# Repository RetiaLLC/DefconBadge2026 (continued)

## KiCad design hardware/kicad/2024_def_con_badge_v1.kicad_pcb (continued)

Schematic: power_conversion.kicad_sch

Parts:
C13, C14, C15, C18, C19: 10uF; C_0603_1608Metric_Pad1.08x0.95mm_HandSolder; LCSC Part # C326057
C16: 4.7uF; C_0603_1608Metric_Pad1.08x0.95mm_HandSolder; LCSC Part # C326580
C17: 0.1uF; C_0603_1608Metric_Pad1.08x0.95mm_HandSolder; LCSC Part # C92490
D10: D; D_SMA; LCSC Part # C50645
L1: 1uH; koher_MDA4020_series_inductor; LCSC Part # C2847468
L2: 2.2uH; koher_MDA4020_series_inductor; LCSC Part # C2847469
Q4: Q_NMOS_GSD; LCSC_SOT-23; LCSC Part # C91714
R27: 750K; R_0603_1608Metric_Pad0.98x0.95mm_HandSolder; LCSC Part # C137684
R28, R31: 100K; R_0603_1608Metric_Pad0.98x0.95mm_HandSolder; LCSC Part # C14675
R30: 453K; R_0603_1608Metric_Pad0.98x0.95mm_HandSolder; LCSC Part # C227908
R32: 330R; R_0603_1608Metric_Pad0.98x0.95mm_HandSolder; LCSC Part # C105881
R33, R34: 10K; R_0603_1608Metric_Pad0.98x0.95mm_HandSolder; LCSC Part # C98220
U4: TPS61023DRLR; TI_CONVERTER_SOT563; LCSC Part # C919459
U5: TLV62569DBV; LCSC_SOT-23-5; LCSC Part # C141836

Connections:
+3.3V: C18.1, C19.1, L2.2, R30.1; also elsewhere on the board
+5V: C14.1, C15.1, C16.1, C17.1, D10.1 (K), R27.1, U4.6 (VOUT), U5.1 (EN), U5.4 (VIN); also elsewhere on the board
/buttons/+BATT: C13.1, L1.1, R34.1, U4.3 (VIN); also elsewhere on the board
/buttons/+USB_IN: D10.2 (A), R32.1; also elsewhere on the board
/power_conversion/stepup_conv_en: Q4.3 (D), R34.2, U4.2 (EN)
GND: C13.2, C14.2, C15.2, C16.2, C17.2, C18.2, C19.2, Q4.2 (S), R28.2, R31.2, R33.1, U4.4 (GND), U5.2 (GND); also elsewhere on the board
unnamed: Q4.1 (G), R32.2, R33.2
unnamed: R27.2, R28.1, U4.1 (FB)
unnamed: L1.2, U4.5 (SW)
unnamed: R30.2, R31.1, U5.5 (FB)
unnamed: L2.1, U5.3 (SW)

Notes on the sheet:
step-down
step-up
diode
"R2"
+5v
0.6 * [1 + (453k/100k)] = 3.318V
Vref = 0.6V [(5/0.6) - 1]*100k = 733kohm
STEP-UP CONVERTER
STEP-DOWN CONVERTER
"R1"
R1/R2 need to be 0.1% resistors to ensure output accuracy
Set to 5.1V to ensure biasing of diode with usb power
-----General concept for power layout----- Diode prevents fighting between usb and dc/dc converter step-up converter only on when usb power is disconnected
AAs
STEP-UP CONVERTER ENABLE
USB POWER
usb
+3.3v

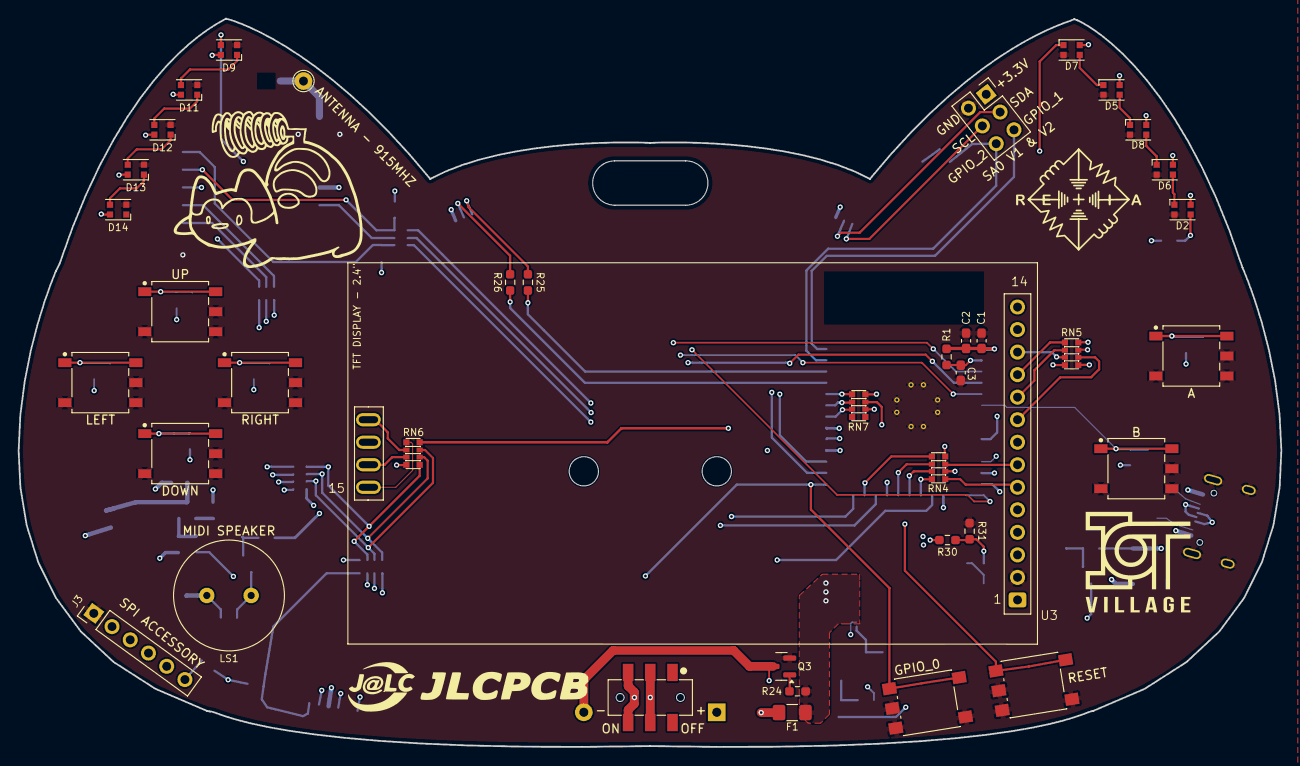
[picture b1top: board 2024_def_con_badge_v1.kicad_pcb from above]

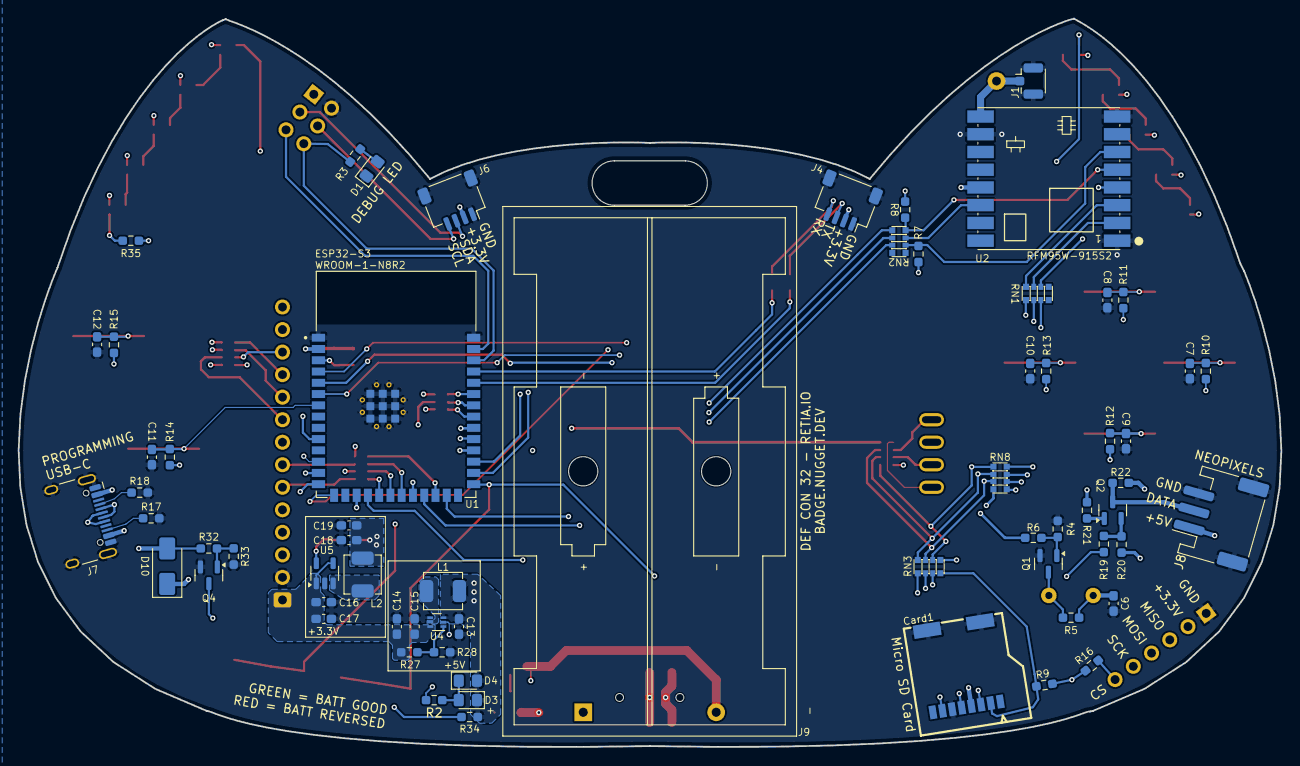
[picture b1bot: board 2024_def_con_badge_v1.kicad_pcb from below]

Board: 4 copper layers, 142.4 x 82.1 mm, 104 parts (65 on the bottom side), 98 nets.

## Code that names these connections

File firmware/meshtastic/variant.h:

#pragma once

// --- Pin Definitions (Matching 2024 Def Con Badge v1) ---
#define PIN_LED_DEBUG 2      // green LED
#define PIN_CS_ACCESSORY -1  // not used

// --- SPI Pins (Shared by Radio and TFT Display) ---
#define PIN_SPI_SCK 13
#define PIN_SPI_MISO 12
#define PIN_SPI_MOSI 11
#define PIN_SPI_CS 48

// --- I2C ---
// Not used, but let's define defaults to avoid compilation warnings
#define PIN_I2C0_SCL 36
#define PIN_I2C0_SDA 35
#define I2C_SDA PIN_I2C0_SDA
#define I2C_SCL PIN_I2C0_SCL

// --- Heartbeat Status LED ---
#define LED_POWER PIN_LED_DEBUG
#define LED_STATE_ON 1

// --- Performance & Feature Defaults ---
#define AMBIENT_LIGHTING_AUTO_START

// --- RGB NeoPixel (Ambient Lighting) ---
#define HAS_NEOPIXEL 1
#define NEOPIXEL_COUNT 10
#define NEOPIXEL_DATA 17
#define NEOPIXEL_TYPE (NEO_GRB + NEO_KHZ800)
#define ENABLE_AMBIENT_LIGHTING

// --- Radio Setup (RFM95W) ---
#define USE_RF95
#define LORA_SCK PIN_SPI_SCK
#define LORA_MISO PIN_SPI_MISO
#define LORA_MOSI PIN_SPI_MOSI
#define LORA_CS PIN_SPI_CS
#define LORA_RESET 38
#define LORA_DIO0 21
#define LORA_DIO1 RADIOLIB_NC
#define LORA_DIO2 RADIOLIB_NC

// --- Buzzer ---
#define PIN_BUZZER 9
#define USE_PIN_BUZZER

// --- Navigation Buttons (using Trackball Input Broker) ---
#define HAS_TRACKBALL 1
#define TB_LEFT 3       // SW3
#define TB_UP 4         // SW4
#define TB_DOWN 5       // SW5
#define TB_RIGHT 6      // SW6
#define TB_PRESS 8      // SW8 (Button A)
#define TB_DIRECTION FALLING

#define BUTTON_PIN 8    // Map main user button to SW8 (Button A)
#define BUTTON_NEED_PULLUP

// --- ILI9341 TFT Display Config ---
#define ILI9341_DRIVER
#define USE_TFTDISPLAY 1
#define TFT_WIDTH 240
#define TFT_HEIGHT 320
#define SCREEN_ROTATE
#define TFT_OFFSET_X 0
#define TFT_OFFSET_Y 0
#define TFT_BUSY -1
#define ILI9341_SPI_HOST SPI2_HOST
#define TFT_SCLK PIN_SPI_SCK
#define TFT_MOSI PIN_SPI_MOSI
#define TFT_MISO PIN_SPI_MISO
#define TFT_CS 47       // CS_TFT_SCREEN
#define TFT_DC 40       // DC_TFT_SCREEN
#define TFT_RST 41      // RESET_TFT_SCREEN
#define TFT_BL -1       // Backlight hardwired to 3.3V
#define SPI_FREQUENCY 40000000
#define SPI_READ_FREQUENCY 16000000
